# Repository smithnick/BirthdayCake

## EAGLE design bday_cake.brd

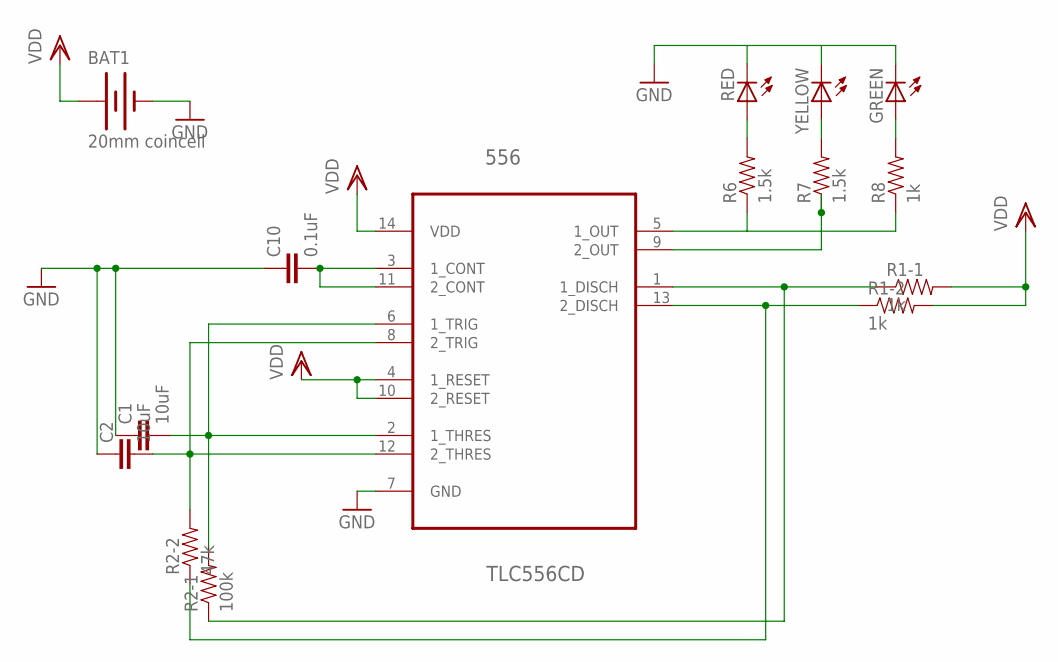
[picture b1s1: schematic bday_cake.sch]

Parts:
556: TLC556CD; SOIC127P600X175-14N
BAT1: 20mm coincell; CR2032_HOLDER
C1, C2: 10uF; 0805
C10: 0.1uF; 0805
GREEN: LEDSMT1206; 1206
R1-1, R1-2, R8: 1k; 0805
R2-1: 100k; 0805
R2-2: 47k; 0805
R6, R7: 1.5k; 0805
RED: LEDSMT1206; 1206
YELLOW: LEDSMT1206; 1206

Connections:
1DISCH: 556.1 (1_DISCH), R1-1.1, R2-1.1
1OUT: 556.5 (1_OUT), R6.1, R8.1
1TRIGTHRESH: 556.2 (1_THRES), 556.6 (1_TRIG), C1.2, R2-1.2
2DISCH: 556.13 (2_DISCH), R1-2.1, R2-2.1
2OUT: 556.9 (2_OUT), R7.1
2TRIGTHRESH: 556.8 (2_TRIG), 556.12 (2_THRES), C2.2, R2-2.2
CONT: 556.3 (1_CONT), 556.11 (2_CONT), C10.2
GND: 556.7 (GND), BAT1.CENTER (-), C1.1, C2.1, C10.1, GREEN.C, RED.C, YELLOW.C
unnamed: R6.2, RED.A
unnamed: R7.2, YELLOW.A
unnamed: GREEN.A, R8.2
VDD: 556.4 (1_RESET), 556.10 (2_RESET), 556.14 (VDD), BAT1.VDD1 (+), BAT1.VDD2 (+), R1-1.2, R1-2.2

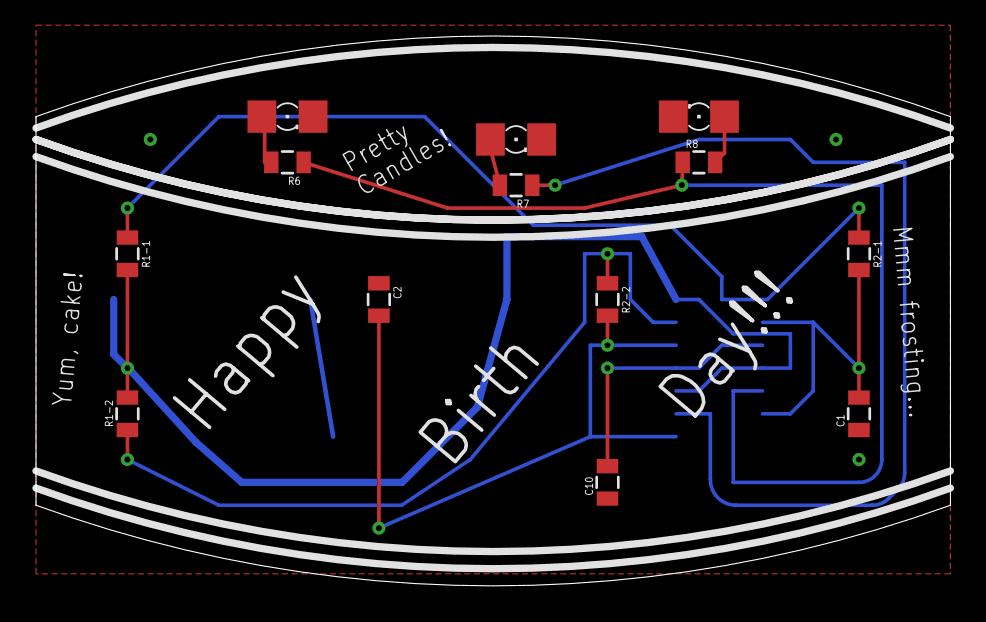
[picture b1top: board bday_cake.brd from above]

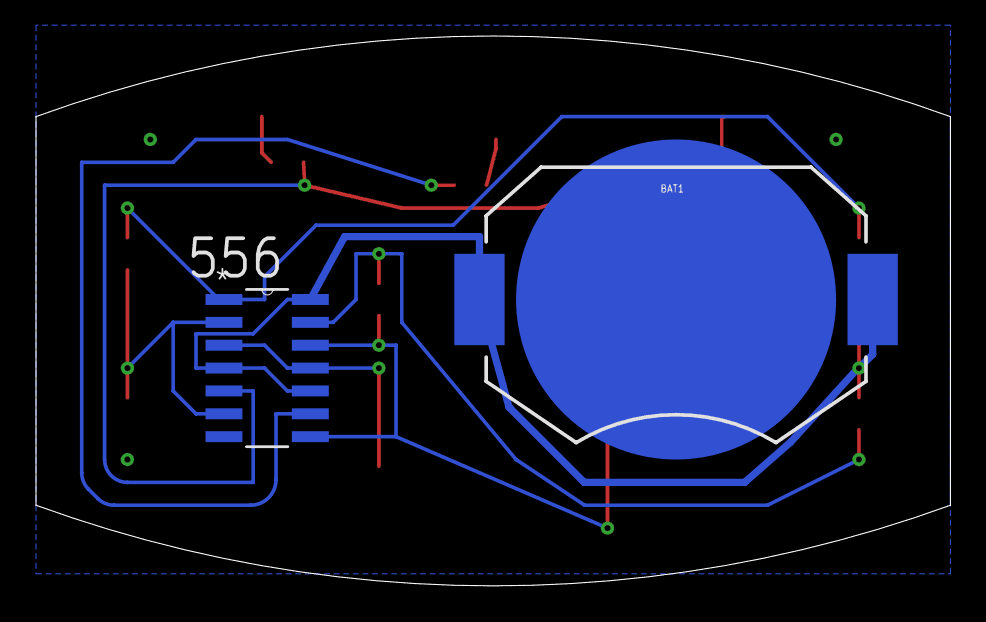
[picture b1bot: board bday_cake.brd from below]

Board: 2 copper layers, 50.8 x 30.5 mm, 15 parts (2 on the bottom side), 12 nets.

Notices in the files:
parts and their libraries:
SparkFun-Passives: Licensing: Creative Commons ShareAlike 4.0 International - https://creativecommons.org/licenses/by-sa/4.0
